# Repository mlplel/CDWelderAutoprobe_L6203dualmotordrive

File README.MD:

KiCad files for the motor control PC board

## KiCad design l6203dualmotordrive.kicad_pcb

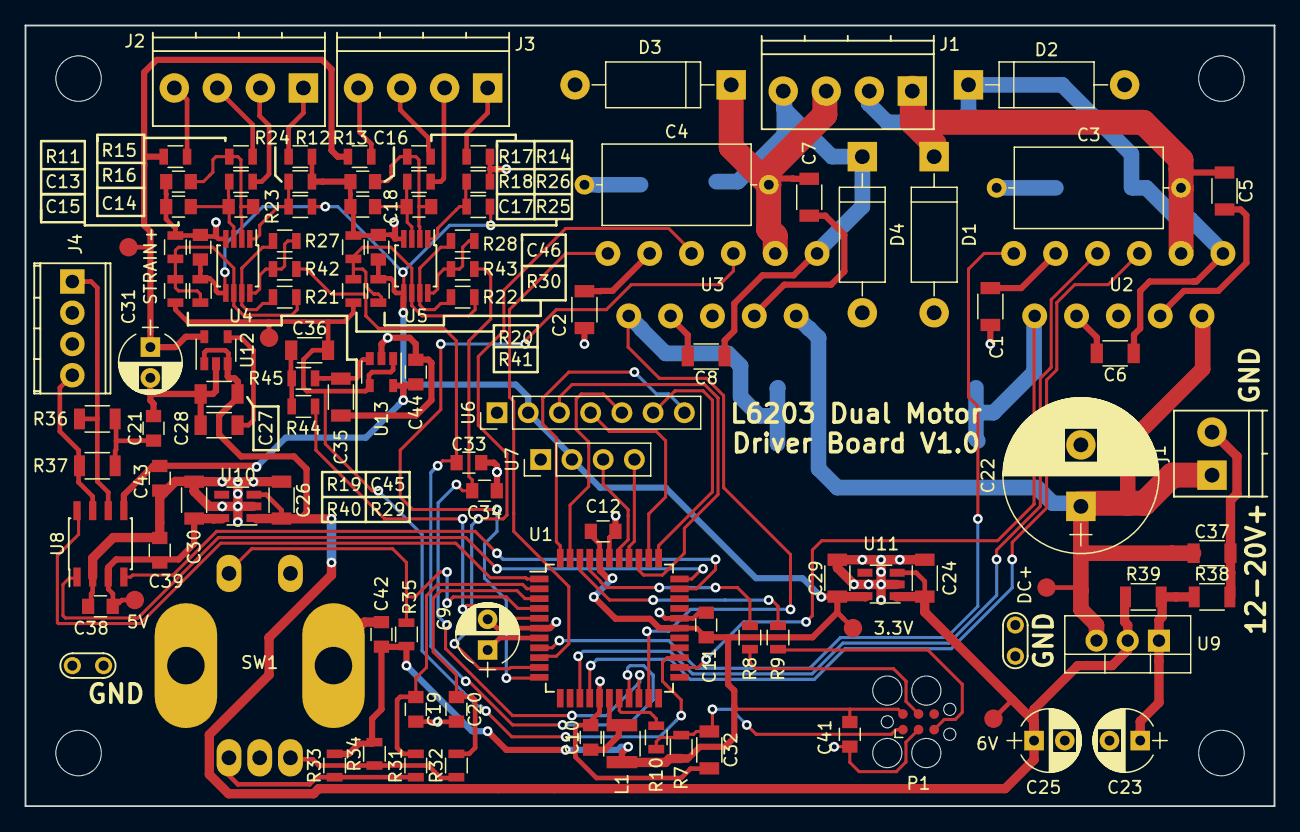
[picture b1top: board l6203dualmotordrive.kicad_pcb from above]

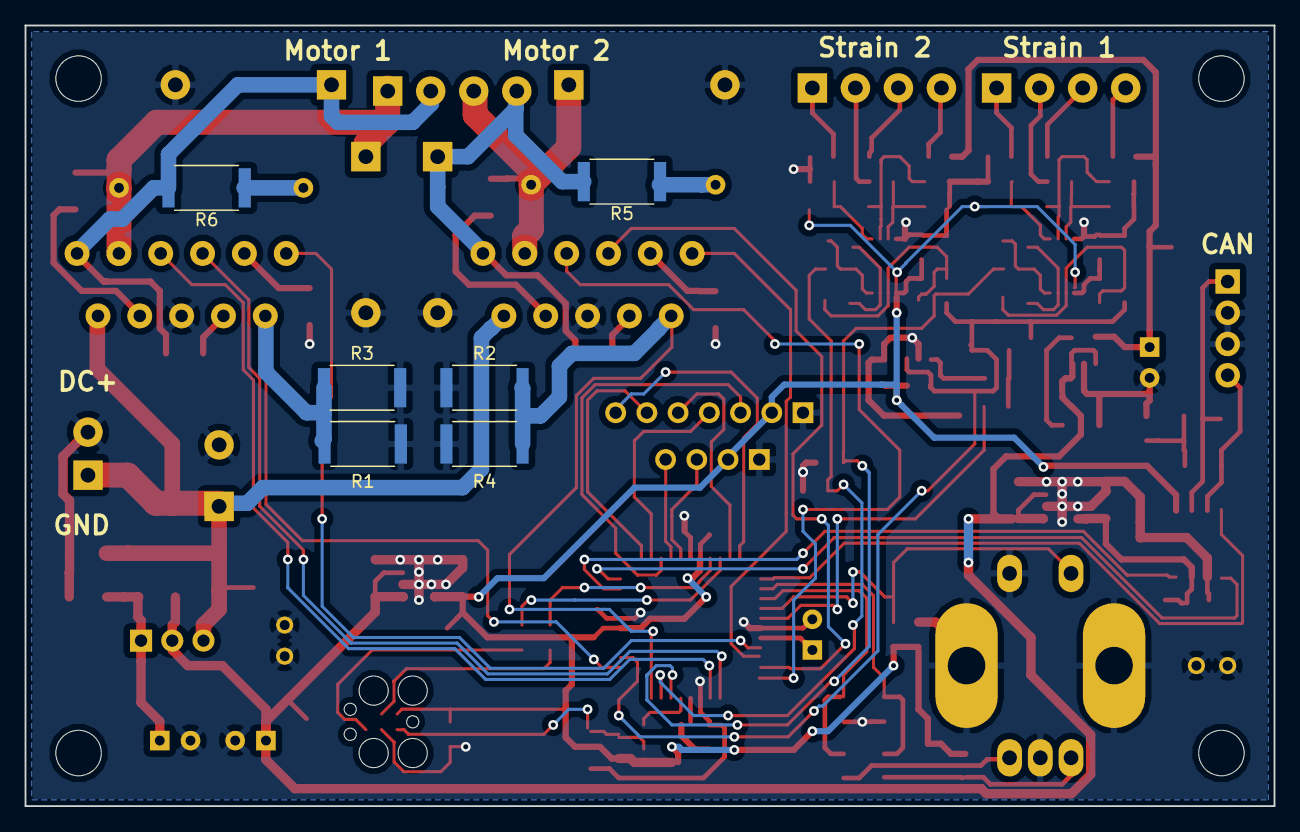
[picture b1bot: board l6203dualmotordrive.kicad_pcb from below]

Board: 2 copper layers, 101.6 x 63.5 mm, 120 parts (6 on the bottom side), 80 nets.

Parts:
3.3V, 5V, 6V: Measurement_Point_Round-SMD-Pad_Small
C1, C2, C5, C6, C7, C8, C24, C26, C29, C30, C35, C36, C37: C; C_1206
C3, C4: C; C_Axial_L12.0mm_D6.5mm_P15.00mm_Horizontal
C9, C23, C25, C31: CP; CP_Radial_D5.0mm_P2.50mm
C10, C11, C12, C19, C20, C21, C33, C34, C38, C39, C41, C42, C43, C44, C45, C46: C; C_0805
C13, C14, C15, C16, C17, C18: C_Small; C_0805
C22: CP; CP_Radial_D12.5mm_P5.00mm
C27, C28, C32: C_Small; C_1206
D1, D2, D3, D4: D; D_DO-15_P12.70mm_Horizontal
DC+: Measurement_Point_Round-SMD-Pad_Small
J1: Conn_01x04; TerminalBlock_Phoenix_PT-3.5mm_4pol
J2, J3: Screw_Terminal_01x04; TerminalBlock_Phoenix_PT-3.5mm_4pol
J4: Conn_01x04_Male; TerminalBlock_Phoenix_MPT-2.54mm_4pol
L1: LPower; C_1210
P1: TC2030-MCP; Tag-Connect_TC2030-IDC-FP
R1, R2, R3, R4, R5, R6: R; R_2512
R7, R8, R9, R10, R11, R12, R13, R14, R15, R16, R17, R18, R19, R20, R21, R22, R23, R24, R25, R26, R27, R28, R29, R30, R31, R32, R33, R34, R35, R40, R41, R42, R43, R44, R45: R; R_0805
R36, R37, R38, R39: R; R_1206
STRAIN+: Measurement_Point_Round-SMD-Pad_Small
SW1: PEC12R-2225F-S0024; PEC12R-4xxxF-Sxxx
U1: dsPIC33EP128MC504; TQFP-44_10x10mm_Pitch0.8mm
U2, U3: L6203; Multiwatt11
U4, U5: AD8237ARMZ; MSOP-8_3x3mm_Pitch0.65mm
U6: spioled128x64; Socket_Strip_Straight_1x07_Pitch2.54mm
U7: i2coled128x64; Socket_Strip_Straight_1x04_Pitch2.54mm
U8: ATA6561; SOIC-8_3.9x4.9mm_Pitch1.27mm
U9: LM317_3PinPackage; TO-220-3_Vertical
U10: NCP718ASN500T1G; TSOT-23-5
U11: NCP718ASN330T1G; TSOT-23-5
U12: MIC5205-5.0; SOT-23-5
U13: TS507CLT; SOT-23-5
j1: PowerScrewTerm; TerminalBlock_Phoenix_PT-3.5mm_2pol

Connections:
+3V3: 3.3V.1, C11.1, C12.1, C29.1, C41.1, C42.1, C43.1, C44.1, C45.1, C46.1, L1.1, P1.2, R7.2, R23.1, R25.1, R29.1, R30.1, R33.2, R34.2, R35.2, U1.28, U1.40, U4.5, U5.5, U6.2, U7.2, U8.5, U11.5, U13.5
+5V: 5V.1, C30.1, C38.1, C39.1, U8.3, U10.5
+6V: 6V.1, C24.1, C25.1, C26.1, C27.1, R39.1, U9.2, U10.1, U10.3, U11.1, U11.3, U12.1, U12.3
/MC1: U1.15, U2.5
/MC2: U1.14, U2.7
/MC3: U1.11, U3.5
/MC4: U1.10, U3.7
/MC5: U1.9, U3.11
/MC6: U1.8, U2.11
/MC7: R1.1, R3.1, U1.24, U2.10
/MC8: R2.1, R4.1, U1.21, U3.10
/control/DISPCS: U1.44, U6.7
/control/DSPRST: U1.43, U6.5
/control/ENCA: C19.1, R31.2, U1.2
/control/ENCB: C20.1, R32.2, U1.3
/control/ENCSW: R35.1, SW1.S1, U1.4
/control/SCK: U1.36, U6.3
/control/SCL: U1.38, U7.3
/control/SDA: U1.37, U7.4
/control/SDI: U1.35, U6.4
/control/SDO: U1.34, U6.6
/io/CANRX: U1.32, U8.4
/io/CANSTBY: U1.1, U8.8
/io/CANTX: U1.33, U8.1
/pressuresense/PRES1: C33.1, R42.1, U1.19
/pressuresense/PRES2: C34.1, R43.1, U1.20
/pressuresense/VREF: C36.1, R40.1, R41.1, U1.25, U13.1, U13.4
/pressuresense/VREFPMW: R44.2, U1.5
GND: C1.2, C2.2, C9.2, C10.2, C11.2, C12.2, C13.1, C15.2, C16.1, C18.2, C19.2, C20.2, C21.2, C22.2, C23.2, C24.2, C25.2, C26.2, C27.2, C28.2, C29.2, C30.2, C31.2, C32.2, C33.2, C34.2, C35.2, C37.2, C38.2, C39.2, C41.2, C42.2, C43.2, C44.2, C45.2, C46.2, D1.2, D2.2, D3.2, D4.2, J4.2, J4.3, P1.3, R1.2, R2.2, R3.2, R4.2, R12.1, R14.1, R19.2, R20.2, R24.1, R26.1, R38.2, SW1.C, SW1.S2, U1.6, U1.16, U1.29, U1.39, U2.6, U3.6, U4.4, U5.4, U6.1, U7.1, U8.2, U10.2, U11.2, U12.2, U13.2, j1.2
unnamed: C1.1, U2.9
unnamed: C2.1, U3.9
unnamed: C3.1, R6.1
unnamed: C3.2, C5.1, D1.1, J1.1, U2.3
unnamed: C4.1, R5.1
unnamed: C4.2, C7.1, D3.1, J1.3, U3.3
unnamed: C5.2, U2.4
unnamed: C6.1, D2.1, J1.2, R6.2, U2.1
unnamed: C6.2, U2.8
unnamed: C7.2, U3.4
unnamed: C8.1, D4.1, J1.4, R5.2, U3.1
unnamed: C8.2, U3.8
unnamed: C9.1, U1.7
unnamed: C10.1, L1.2, U1.17
unnamed: C13.2, C14.1, R15.1, U4.2
unnamed: C14.2, C15.1, R16.1, U4.3
unnamed: C16.2, C17.1, R17.1, U5.2
unnamed: C17.2, C18.1, R18.1, U5.3
unnamed: C21.1, R36.1, R37.1
unnamed: C23.1, R38.1, R39.2, U9.1
unnamed: C28.1, U12.4
unnamed: C32.1, P1.1, R7.1, R10.2
unnamed: C35.1, R45.1, U13.3
unnamed: C36.2, R44.1, R45.2
unnamed: J2.1, R12.2
unnamed: J2.2, R16.2
unnamed: J2.3, R15.2
unnamed: J2.4, R11.2
unnamed: J3.1, R14.2
unnamed: J3.2, R18.2
unnamed: J3.3, R17.2
unnamed: J3.4, R13.2
unnamed: J4.1, R36.2, U8.6
unnamed: J4.4, R37.2, U8.7
unnamed: P1.4, R8.2
unnamed: P1.5, R9.2
unnamed: R10.1, U1.18
unnamed: R19.1, R21.2, R29.2, R40.2, U4.6
unnamed: R20.1, R22.2, R30.2, R41.2, U5.6
unnamed: R21.1, R27.2, U4.7
unnamed: R22.1, R28.2, U5.7
unnamed: R23.2, R24.2, U4.1
unnamed: R25.2, R26.2, U5.1
unnamed: R27.1, R42.2, U4.8
unnamed: R28.1, R43.2, U5.8
unnamed: R31.1, R33.1, SW1.A
unnamed: R32.1, R34.1, SW1.B
PGC: R9.1, U1.42
PGD: R8.1, U1.41
VAA: C31.1, R11.1, R13.1, STRAIN+.1, U12.5
VCC: C22.1, C37.1, DC+.1, U2.2, U3.2, U9.3, j1.1

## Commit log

2023-01-13 current working version
